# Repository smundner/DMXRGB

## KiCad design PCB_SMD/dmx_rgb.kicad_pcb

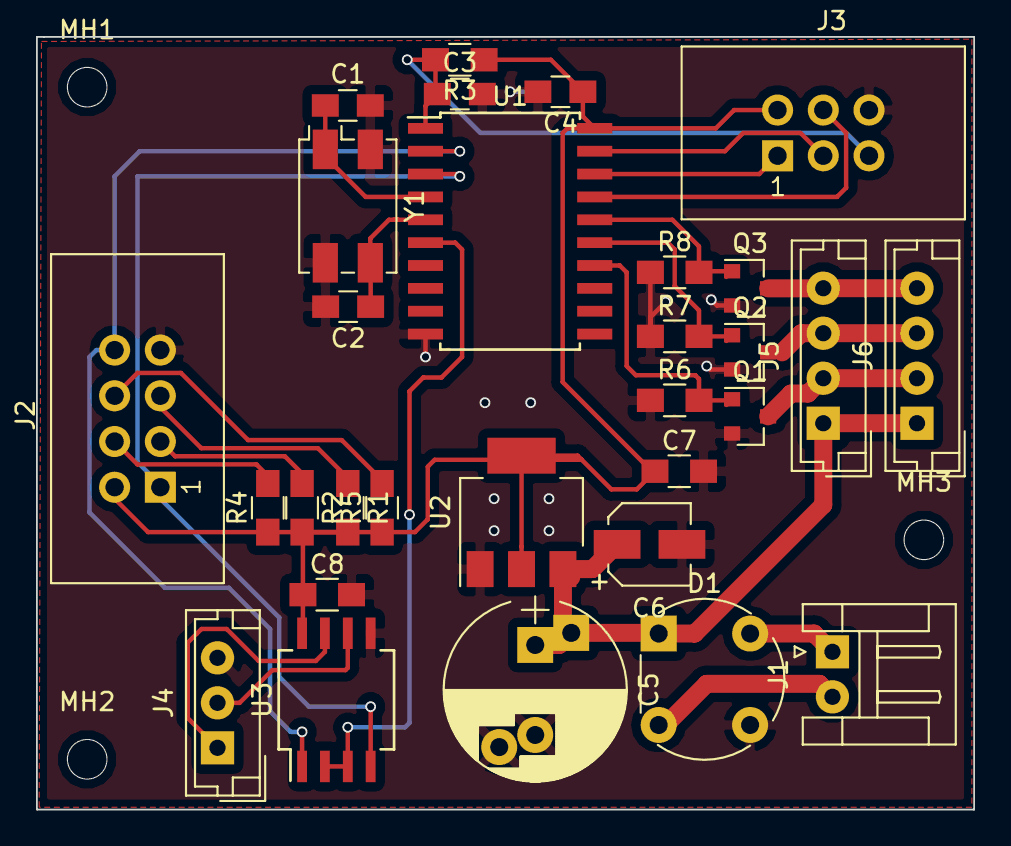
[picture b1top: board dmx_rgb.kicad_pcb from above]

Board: 2 copper layers, 52.1 x 42.9 mm, 33 parts (0 on the bottom side), 26 nets.

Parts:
C1, C2, C3, C4: C; C_0805_HandSoldering
C5: CP; CP_Radial_D10.0mm_P5.00mm_P7.50mm
C6: CP; CP_Elec_4x5.8
C7, C8: C; R_0805_HandSoldering
D1: D_Bridge_+A-A; Diode_Bridge_Round_D8.9mm
J1: CONN_01X02; JST_EH_S02B-EH_02x2.50mm_Angled
J2: Conn_02x04_Odd_Even; IDC_Header_Straight_8pins
J3: Conn_02x03_Odd_Even; IDC_Header_Straight_6pins
J4: CONN_01X03; JST_EH_B03B-EH-A_03x2.50mm_Straight
J5, J6: CONN_01X04; JST_EH_B04B-EH-A_04x2.50mm_Straight
MH1, MH2, MH3: MountingHole; MountingHole_2.2mm_M2
Q1, Q2, Q3: Q_NMOS_GSD; SOT-23
R1, R2, R3, R4, R5, R7, R8: R; R_0805_HandSoldering
R6: 10k; R_0805_HandSoldering
U1: ATTINY2313-20PU; SOIC-20W_7.5x12.8mm_Pitch1.27mm
U2: LM1117-3.3; SOT-223-3Lead_TabPin2
U3: MAX485E; SO-8_5.3x6.2mm_Pitch1.27mm
Y1: Crystal_GND24; Crystal_SMD_EuroQuartz_MQ-4pin_7.0x5.0mm

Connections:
+12V: C5.1, C6.1, D1.1, J5.1, J6.1, U2.3
/DIR: U1.6, U3.2, U3.3
/MISO: J3.1, U1.18
/MOSI/SDA: J3.4, U1.17
/PWM1: Q1.1, R6.2, U1.14
/PWM2: Q2.1, R7.2, U1.15
/PWM3: Q3.1, R8.2, U1.16
/RESET: C3.1, J3.5, R3.2, U1.1
/RXD: J2.8, U1.2, U3.1
/SCL/SCK: J3.3, U1.19
/TXD: J2.1, U1.3, U3.4
GND: C1.2, C2.2, C3.2, C4.2, C5.2, C6.2, C7.2, C8.2, D1.3, J2.7, J3.6, J4.3, Q1.2, Q2.2, Q3.2, R6.1, R7.1, R8.1, U1.10, U2.1, U3.5, Y1.2, Y1.4
unnamed: C1.1, U1.4, Y1.1
unnamed: C2.1, U1.5, Y1.3
unnamed: D1.2, J1.2
unnamed: D1.4, J1.1
unnamed: J2.3, R2.1
unnamed: J2.4, R4.2
unnamed: J2.5, R1.1
unnamed: J2.6, R5.2
unnamed: J4.1, U3.7
unnamed: J4.2, U3.6
unnamed: J5.2, J6.2, Q1.3
unnamed: J5.3, J6.3, Q2.3
unnamed: J5.4, J6.4, Q3.3
VCC: C4.1, C7.1, C8.1, J2.2, J3.2, R1.2, R2.2, R3.1, R4.1, R5.1, U1.20, U2.2, U3.8

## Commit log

2017-11-28 inital
2017-11-28 Create LICENSE
2018-01-02 BOX
    add a box for the PCB
2018-01-04 add screw holes add Wifif project
2018-01-07 clean up
    Cleand not needed files and rename the WiFi sketch
2018-01-08 optimize the box for printing
2018-01-09 add makefile
2018-01-09 Controler programm hinzugefügt
2018-01-10 Fehler in der USART init auf beiden seiten behoben
2018-01-11 Rev 1.0
    The Wifi bridge is running with the rib controller
2018-01-13 add dmx function
2018-02-03 add smd pcb
2018-03-19 Board geändert
2018-04-20 fix pwm
    change pwm to phase correct pwm
2018-08-24 spannungs wandler getauscht
2018-09-18 node red mqtt json upgrade
2018-09-19 add mqtt broker user and password
2018-09-20 add git ignorer
2018-09-21 running device
